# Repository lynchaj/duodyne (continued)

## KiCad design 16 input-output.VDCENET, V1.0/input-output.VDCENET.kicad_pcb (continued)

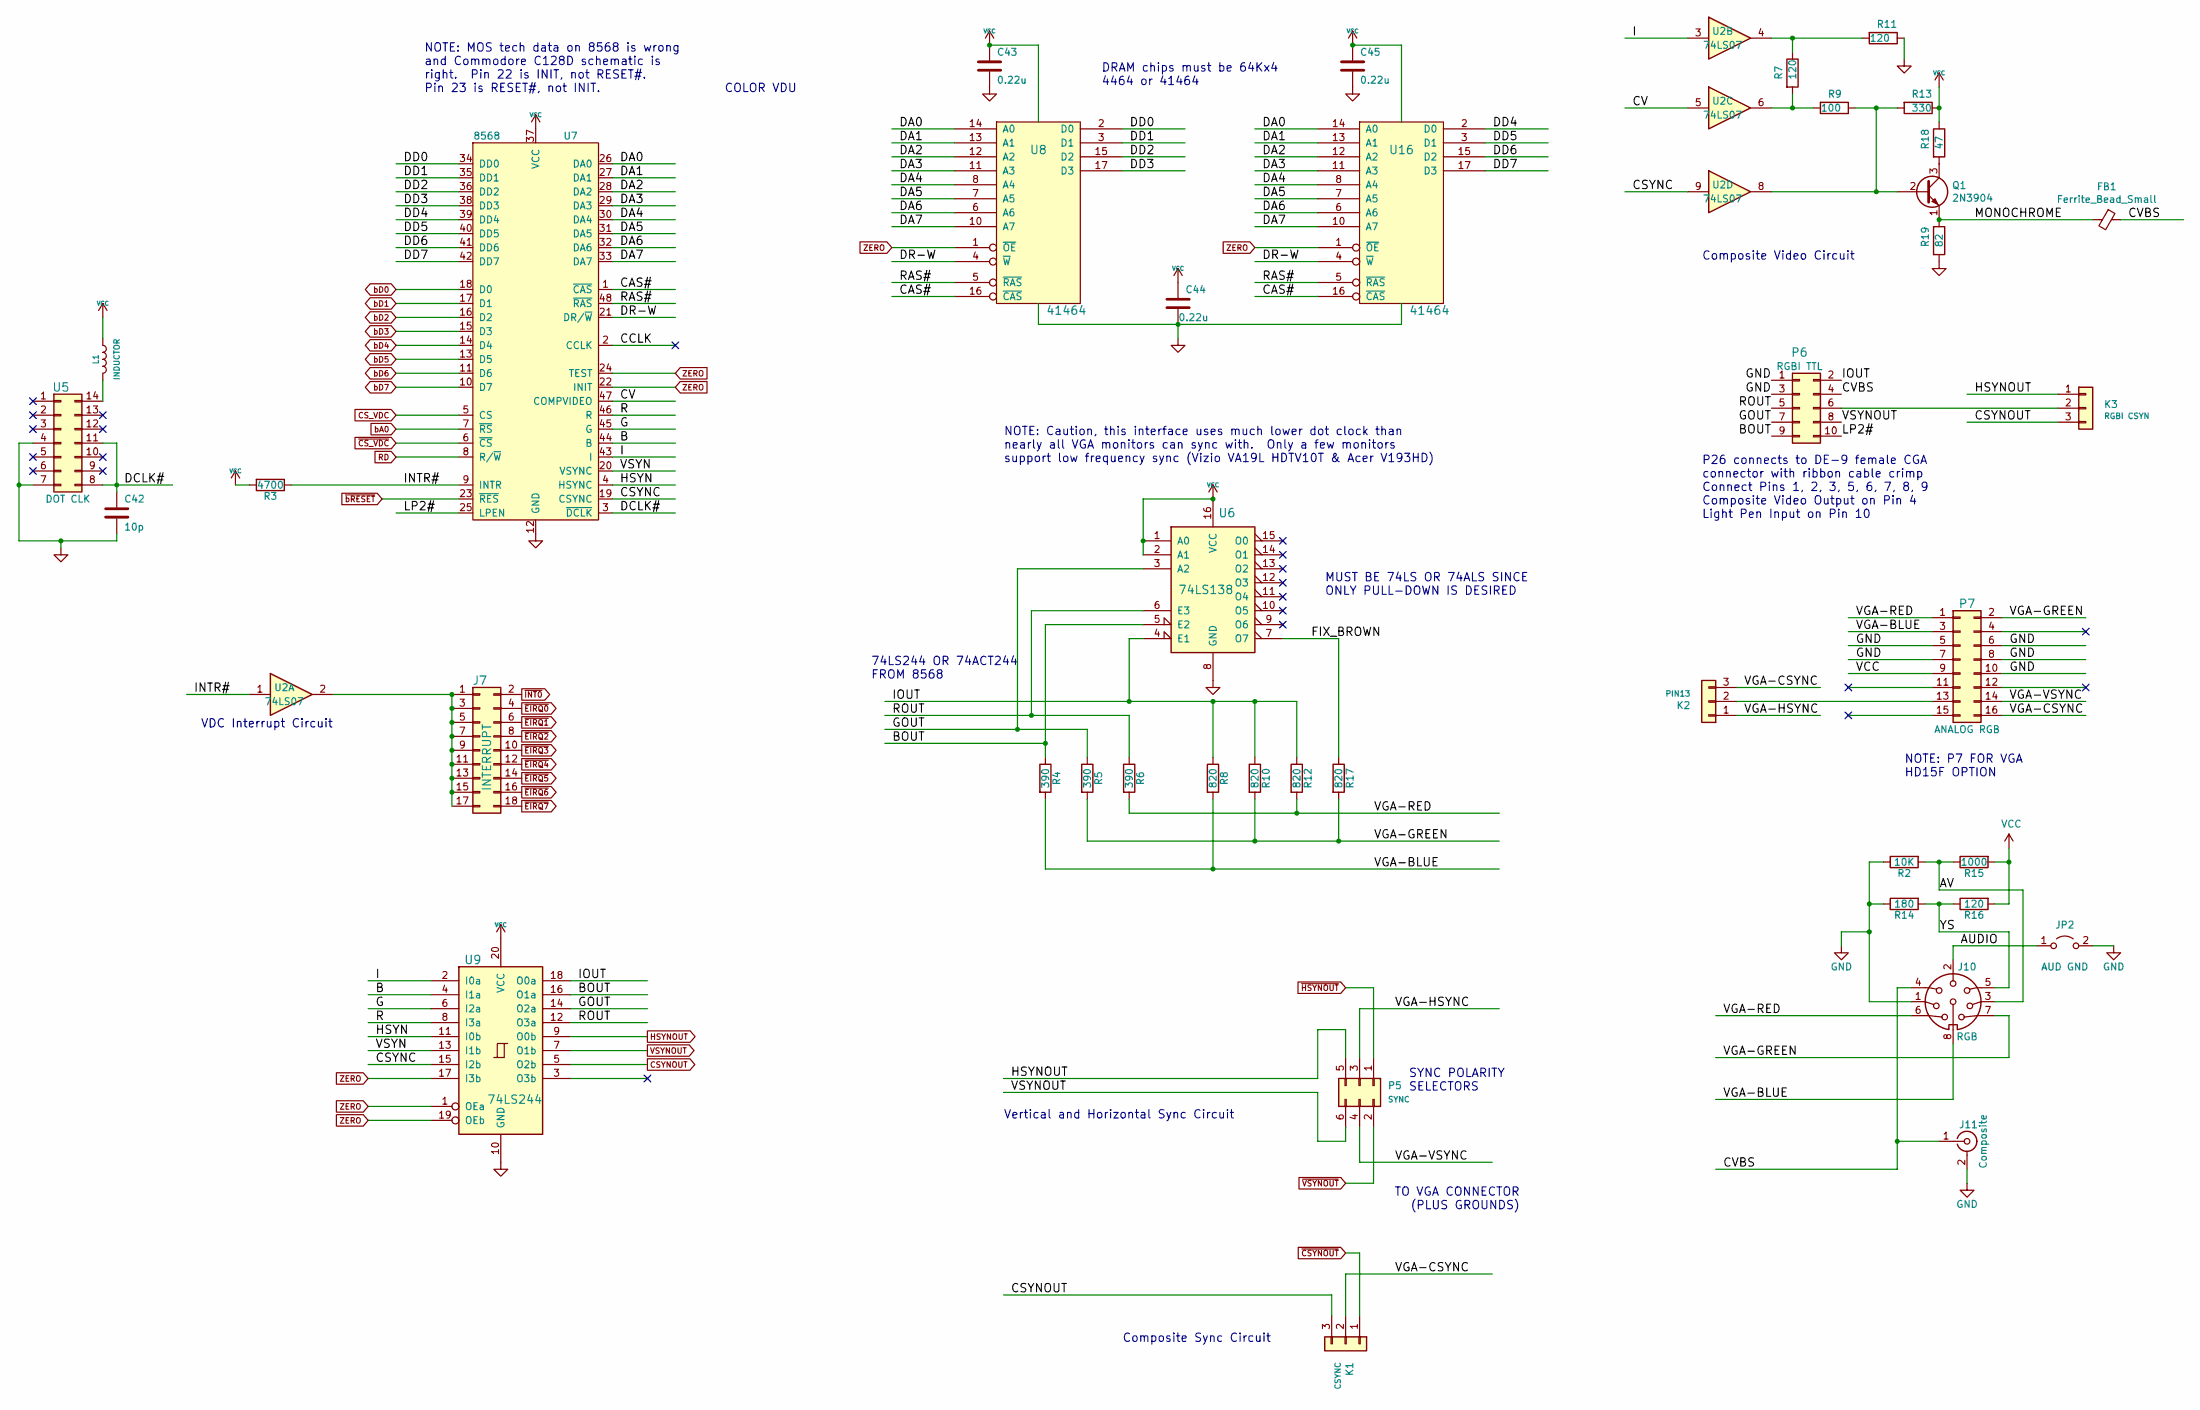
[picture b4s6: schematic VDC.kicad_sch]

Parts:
C42: 10p; C_Disc_D5.0mm_W2.5mm_P5.00mm
C43, C44, C45: 0.22u; C_Disc_D5.0mm_W2.5mm_P5.00mm
FB1: Ferrite_Bead_Small; LairdTech_28C0236-0JW-10
J7: INTERRUPT; PinHeader_2x09_P2.54mm_Vertical
J10: RGB; Conn_DIN_8pin
J11: Composite; Conn_RCA_Right
JP2: AUD GND; PinHeader_1x02_P2.54mm_Vertical
K1: CSYNC; PinHeader_1x03_P2.54mm_Vertical
K2: PIN13; PinHeader_1x03_P2.54mm_Vertical
K3: RGBI CSYN; PinHeader_1x03_P2.54mm_Vertical
L1: INDUCTOR; L_Axial_L6.6mm_D2.7mm_P10.16mm_Horizontal_Vishay_IM-2
P5: SYNC; PinHeader_2x03_P2.54mm_Vertical
P6: RGBI TTL; IDC-Header_2x05_P2.54mm_Horizontal
P7: ANALOG RGB; IDC-Header_2x08_P2.54mm_Horizontal
Q1: 2N3904; TO-92L_Inline
R2: 10K; R_Axial_DIN0207_L6.3mm_D2.5mm_P7.62mm_Horizontal
R3: 4700; R_Axial_DIN0207_L6.3mm_D2.5mm_P7.62mm_Horizontal
R4, R5, R6: 390; R_Axial_DIN0207_L6.3mm_D2.5mm_P7.62mm_Horizontal
R7, R11, R16: 120; R_Axial_DIN0207_L6.3mm_D2.5mm_P7.62mm_Horizontal
R8, R10, R12, R17: 820; R_Axial_DIN0207_L6.3mm_D2.5mm_P7.62mm_Horizontal
R9: 100; R_Axial_DIN0207_L6.3mm_D2.5mm_P7.62mm_Horizontal
R13: 330; R_Axial_DIN0207_L6.3mm_D2.5mm_P7.62mm_Horizontal
R14: 180; R_Axial_DIN0207_L6.3mm_D2.5mm_P7.62mm_Horizontal
R15: 1000; R_Axial_DIN0207_L6.3mm_D2.5mm_P7.62mm_Horizontal
R18: 47; R_Axial_DIN0207_L6.3mm_D2.5mm_P7.62mm_Horizontal
R19: 82; R_Axial_DIN0207_L6.3mm_D2.5mm_P7.62mm_Horizontal
U2: 74LS07; DIP-14_W7.62mm
U5: DOT CLK; DIP-14_W7.62mm
U6: 74LS138; DIP-16_W7.62mm
U7: 8568; DIP-48_W15.24mm
U8, U16: 41464; DIP-18_W7.62mm
U9: 74LS244; DIP-20_W7.62mm

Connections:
/VDC/AUDIO: J10.2, JP2.1 (A)
/VDC/AV: J10.3, R2.2, R15.1
/VDC/B: U7.44 (B), U9.4 (I1a)
/VDC/BOUT: P6.9, R4.1, U6.5 (E2), U9.16 (O1a)
/VDC/CAS#: U7.1 (~CAS), U8.16 (~CAS), U16.16 (~CAS)
/VDC/CCLK: U7.2 (CCLK)
/VDC/CSYNC: U2.9, U7.19 (CSYNC), U9.15 (I2b)
/VDC/CV: U2.5, U7.47 (COMPVIDEO)
/VDC/CVBS: FB1.1, J10.4, J11.1 (In), P6.4
/VDC/DA0: U7.26 (DA0), U8.14 (A0), U16.14 (A0)
/VDC/DA1: U7.27 (DA1), U8.13 (A1), U16.13 (A1)
/VDC/DA2: U7.28 (DA2), U8.12 (A2), U16.12 (A2)
/VDC/DA3: U7.29 (DA3), U8.11 (A3), U16.11 (A3)
/VDC/DA4: U7.30 (DA4), U8.8 (A4), U16.8 (A4)
/VDC/DA5: U7.31 (DA5), U8.7 (A5), U16.7 (A5)
/VDC/DA6: U7.32 (DA6), U8.6 (A6), U16.6 (A6)
/VDC/DA7: U7.33 (DA7), U8.10 (A7), U16.10 (A7)
/VDC/DCLK#: C42.1, U5.8, U5.11, U7.3 (~DCLK)
/VDC/DD0: U7.34 (DD0), U8.2 (D0)
/VDC/DD1: U7.35 (DD1), U8.3 (D1)
/VDC/DD2: U7.36 (DD2), U8.15 (D2)
/VDC/DD3: U7.38 (DD3), U8.17 (D3)
/VDC/DD4: U7.39 (DD4), U16.2 (D0)
/VDC/DD5: U7.40 (DD5), U16.3 (D1)
/VDC/DD6: U7.41 (DD6), U16.15 (D2)
/VDC/DD7: U7.42 (DD7), U16.17 (D3)
/VDC/DR-W: U7.21 (DR/~W), U8.4 (~W), U16.4 (~W)
/VDC/FIX_BROWN: R17.1, U6.7 (O7)
/VDC/G: U7.45 (G), U9.6 (I2a)
/VDC/GOUT: P6.7, R5.1, U6.3 (A2), U9.14 (O2a)
/VDC/HSYN: U7.4 (HSYNC), U9.11 (I0b)
/VDC/I: U2.3, U7.43 (I), U9.2 (I0a)
/VDC/INTR#: R3.1, U2.1, U7.9 (INTR)
/VDC/IOUT: P6.2, R8.1, R10.1, R12.1, U6.4 (E1), U9.18 (O0a)
/VDC/LP2#: P6.10, U7.25 (LPEN)
/VDC/MONOCHROME: FB1.2, Q1.1 (E), R19.1
/VDC/R: U7.46 (R), U9.8 (I3a)
/VDC/RAS#: U7.48 (~RAS), U8.5 (~RAS), U16.5 (~RAS)
/VDC/ROUT: P6.5, R6.1, U6.6 (E3), U9.12 (O3a)
/VDC/VGA-BLUE: J10.8, P7.3, R4.2, R8.2
/VDC/VGA-CSYNC: K1.2, K2.3, P7.16
/VDC/VGA-GREEN: J10.7, P7.2, R5.2, R10.2, R17.2
/VDC/VGA-HSYNC: K2.1, P5.3
/VDC/VGA-RED: J10.6, P7.1, R6.2, R12.2
/VDC/VGA-VSYNC: P5.4, P7.14
/VDC/VSYN: U7.20 (VSYNC), U9.13 (I1b)
/VDC/YS: J10.5, R14.2, R16.1
CSYNOUT: K1.3, K3.3, U9.5 (O2b); also elsewhere on the board
CS_VDC: U7.5 (CS); also elsewhere on the board
GND: C42.2, C43.2, C44.2, C45.2, J10.1, J11.2 (Ext), JP2.2 (B), P6.1, P6.3, P7.5, P7.6, P7.7, P7.8, P7.10, R2.1, R11.1, R14.1, R19.2, U5.4, U5.7, U6.8 (GND), U7.12 (GND), U8.18 (GND), U9.10 (GND), U16.18 (GND); also elsewhere on the board
HSYNOUT: K3.1, P5.5, U9.9 (O0b); also elsewhere on the board
unnamed: J7.1, J7.3, J7.5, J7.7, J7.9, J7.11, J7.13, J7.15, J7.17, U2.2
unnamed: K2.2, P7.13
unnamed: K3.2, P6.6
unnamed: L1.2, U5.14
unnamed: Q1.2 (B), R9.1, R13.2, U2.8
unnamed: Q1.3 (C), R18.2
unnamed: R7.2, R9.2, U2.6
unnamed: R7.1, R11.2, U2.4
RD: U7.8 (R/~W); also elsewhere on the board
VCC: C43.1, C44.1, C45.1, L1.1, P7.9, R3.2, R13.1, R15.2, R16.2, R18.1, U6.1 (A0), U6.2 (A1), U6.16 (VCC), U7.37 (VCC), U8.9 (VCC), U9.20 (VCC), U16.9 (VCC); also elsewhere on the board
VSYNOUT: P5.6, P6.8, U9.7 (O1b); also elsewhere on the board
ZERO: U7.22 (INIT), U7.24 (TEST), U8.1 (~OE), U9.1 (OEa), U9.17 (I3b), U9.19 (OEb), U16.1 (~OE); also elsewhere on the board
bA0: U7.7 (~RS); also elsewhere on the board
bD0: U7.18 (D0); also elsewhere on the board
bD1: U7.17 (D1); also elsewhere on the board
bD2: U7.16 (D2); also elsewhere on the board
bD3: U7.15 (D3); also elsewhere on the board
bD4: U7.14 (D4); also elsewhere on the board
bD5: U7.13 (D5); also elsewhere on the board
bD6: U7.11 (D6); also elsewhere on the board
bD7: U7.10 (D7); also elsewhere on the board
~CSYNOUT: K1.1; also elsewhere on the board
~CS_VDC: U7.6 (~CS); also elsewhere on the board
~HSYNOUT: P5.1; also elsewhere on the board
~VSYNOUT: P5.2; also elsewhere on the board
~bRESET: U7.23 (~RES); also elsewhere on the board

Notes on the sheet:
VDC Interrupt Circuit
Composite Sync Circuit
Vertical and Horizontal Sync Circuit
74LS244 OR 74ACT244 FROM 8568
NOTE: Caution, this interface uses much lower dot clock than nearly all VGA monitors can sync with. Only a few monitors support low frequency sync (Vizio VA19L HDTV10T & Acer V193HD)
SYNC POLARITY SELECTORS
Composite Video Circuit
COLOR VDU
DRAM chips must be 64Kx4 4464 or 41464
TO VGA CONNECTOR (PLUS GROUNDS)
P26 connects to DE-9 female CGA connector with ribbon cable crimp Connect Pins 1, 2, 3, 5, 6, 7, 8, 9 Composite Video Output on Pin 4 Light Pen Input on Pin 10
NOTE: P7 FOR VGA HD15F OPTION
MUST BE 74LS OR 74ALS SINCE ONLY PULL-DOWN IS DESIRED
NOTE: MOS tech data on 8568 is wrong and Commodore C128D schematic is right. Pin 22 is INIT, not RESET#. Pin 23 is RESET#, not INIT.

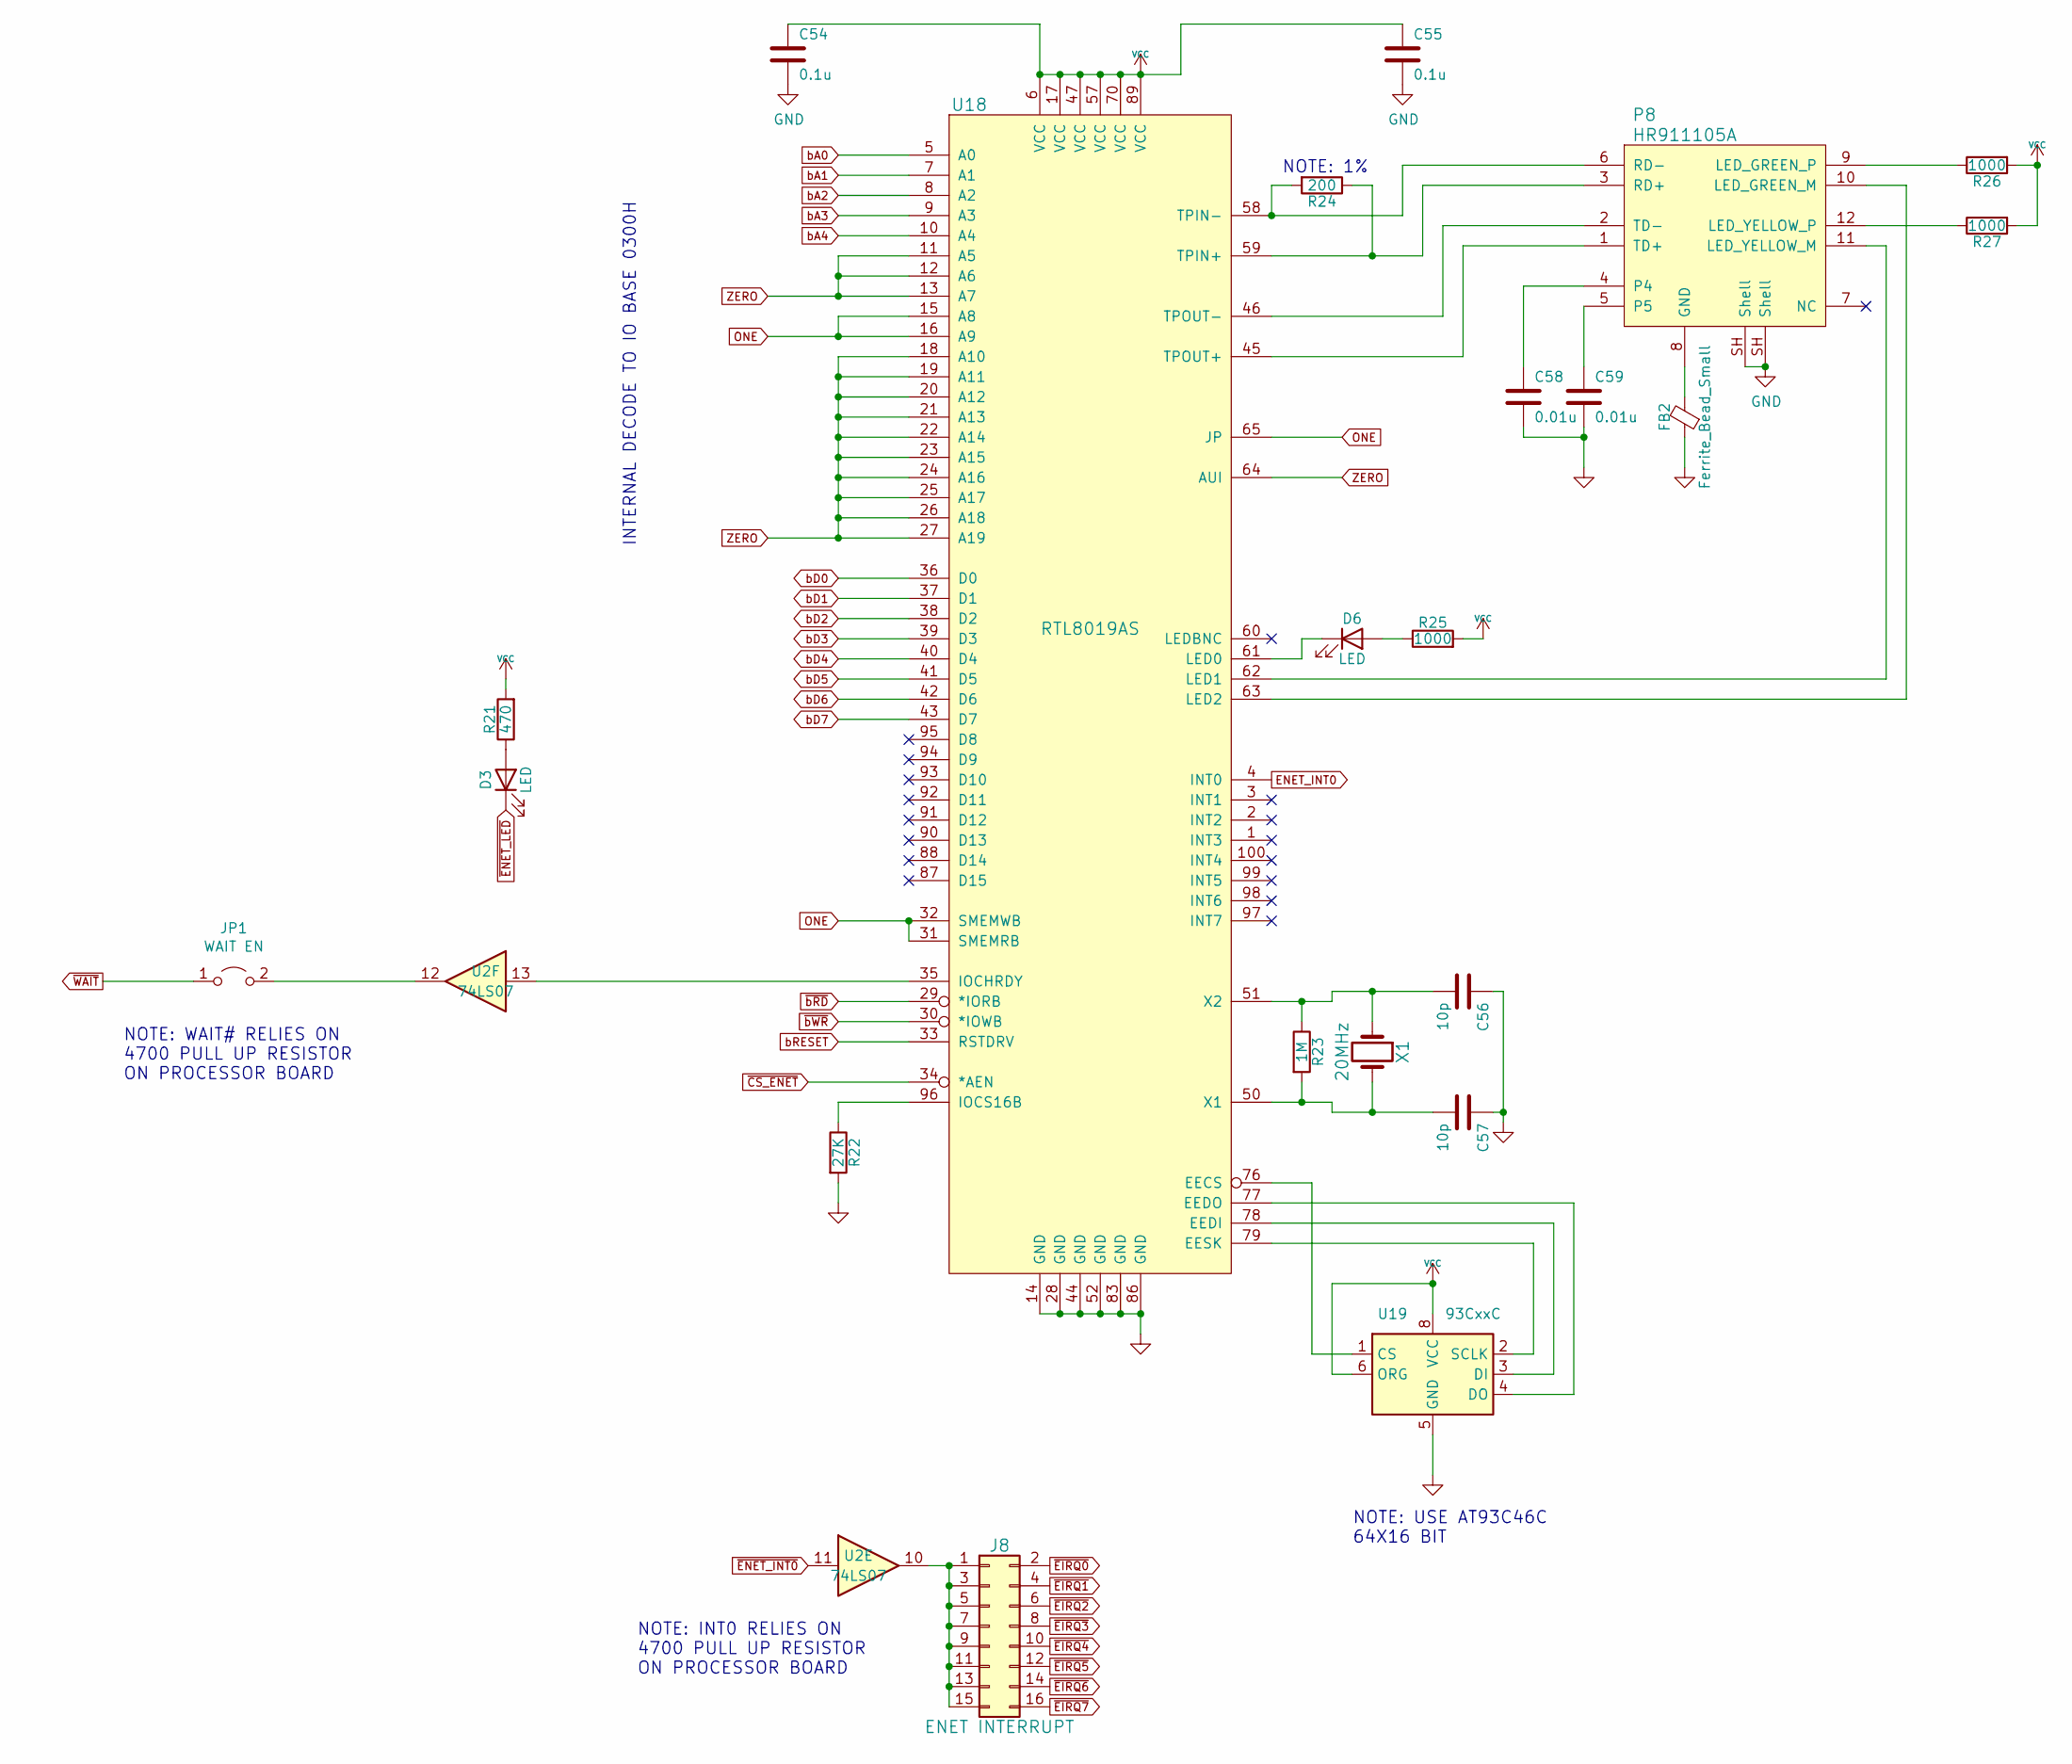
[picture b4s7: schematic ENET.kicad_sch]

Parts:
C54, C55: 0.1u; C_Disc_D5.0mm_W2.5mm_P5.00mm
C56, C57: 10p; C_Disc_D5.0mm_W2.5mm_P5.00mm
C58, C59: 0.01u; C_Disc_D5.0mm_W2.5mm_P5.00mm
D3, D6: LED; LED_D3.0mm_Horizontal_O3.81mm_Z2.0mm
FB2: Ferrite_Bead_Small; LairdTech_28C0236-0JW-10
J8: ENET INTERRUPT; PinHeader_2x08_P2.54mm_Vertical
JP1: WAIT EN; PinHeader_1x02_P2.54mm_Vertical
P8: HR911105A; RJ45_Hanrun_HR911105A
R21: 470; R_Axial_DIN0207_L6.3mm_D2.5mm_P7.62mm_Horizontal
R22: 27K; R_Axial_DIN0207_L6.3mm_D2.5mm_P7.62mm_Horizontal
R23: 1M; R_Axial_DIN0207_L6.3mm_D2.5mm_P7.62mm_Horizontal
R24: 200; R_Axial_DIN0207_L6.3mm_D2.5mm_P7.62mm_Horizontal
R25, R26, R27: 1000; R_Axial_DIN0207_L6.3mm_D2.5mm_P7.62mm_Horizontal
U2: 74LS07; DIP-14_W7.62mm_Socket
U18: RTL8019AS; QFP100-DIP-Adapter
U19: 93CxxC; DIP-8_W7.62mm_Socket
X1: 20MHz; Crystal_HC49-4H_Vertical

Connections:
ENET_INT0: U18.4 (INT0); also elsewhere on the board
GND: C54.2, C55.2, C56.1, C57.1, C58.2, C59.2, FB2.1, P8.SH (Shell), R22.2, U18.14 (GND), U18.28 (GND), U18.44 (GND), U18.52 (GND), U18.83 (GND), U18.86 (GND), U19.5 (GND); also elsewhere on the board
unnamed: C56.2, R23.1, U18.51 (X2), X1.1
unnamed: C57.2, R23.2, U18.50 (X1), X1.2
unnamed: C58.1, P8.4
unnamed: C59.1, P8.5
unnamed: D3.2 (A), R21.1
unnamed: D6.1 (K), U18.61 (LED0)
unnamed: D6.2 (A), R25.1
unnamed: FB2.2, P8.8 (GND)
unnamed: J8.1, J8.3, J8.5, J8.7, J8.9, J8.11, J8.13, J8.15, U2.10
unnamed: JP1.2 (B), U2.12
unnamed: P8.1 (TD+), U18.45 (TPOUT+)
unnamed: P8.2 (TD-), U18.46 (TPOUT-)
unnamed: P8.3 (RD+), R24.1, U18.59 (TPIN+)
unnamed: P8.6 (RD-), R24.2, U18.58 (TPIN-)
unnamed: P8.9 (LED_GREEN_P), R26.1
unnamed: P8.10 (LED_GREEN_M), U18.63 (LED2)
unnamed: P8.11 (LED_YELLOW_M), U18.62 (LED1)
unnamed: P8.12 (LED_YELLOW_P), R27.1
unnamed: R22.1, U18.96 (IOCS16B)
unnamed: U2.13, U18.35 (IOCHRDY)
unnamed: U18.76 (EECS), U19.1 (CS)
unnamed: U18.77 (EEDO), U19.4 (DO)
unnamed: U18.78 (EEDI), U19.3 (DI)
unnamed: U18.79 (EESK), U19.2 (SCLK)
ONE: U18.15 (A8), U18.16 (A9), U18.31 (SMEMRB), U18.32 (SMEMWB), U18.65 (JP); also elsewhere on the board
VCC: C54.1, C55.1, R21.2, R25.2, R26.2, R27.2, U18.6 (VCC), U18.17 (VCC), U18.47 (VCC), U18.57 (VCC), U18.70 (VCC), U18.89 (VCC), U19.6 (ORG), U19.8 (VCC); also elsewhere on the board
ZERO: U18.11 (A5), U18.12 (A6), U18.13 (A7), U18.18 (A10), U18.19 (A11), U18.20 (A12), U18.21 (A13), U18.22 (A14), U18.23 (A15), U18.24 (A16), U18.25 (A17), U18.26 (A18), U18.27 (A19), U18.64 (AUI); also elsewhere on the board
bA0: U18.5 (A0); also elsewhere on the board
bA1: U18.7 (A1); also elsewhere on the board
bA2: U18.8 (A2); also elsewhere on the board
bA3: U18.9 (A3); also elsewhere on the board
bA4: U18.10 (A4); also elsewhere on the board
bD0: U18.36 (D0); also elsewhere on the board
bD1: U18.37 (D1); also elsewhere on the board
bD2: U18.38 (D2); also elsewhere on the board
bD3: U18.39 (D3); also elsewhere on the board
bD4: U18.40 (D4); also elsewhere on the board
bD5: U18.41 (D5); also elsewhere on the board
bD6: U18.42 (D6); also elsewhere on the board
bD7: U18.43 (D7); also elsewhere on the board
bRESET: U18.33 (RSTDRV); also elsewhere on the board
~CS_ENET: U18.34 (*AEN); also elsewhere on the board
~ENET_INT0: U2.11; also elsewhere on the board
~ENET_LED: D3.1 (K); also elsewhere on the board
~WAIT: JP1.1 (A); also elsewhere on the board
~bRD: U18.29 (*IORB); also elsewhere on the board
~bWR: U18.30 (*IOWB); also elsewhere on the board

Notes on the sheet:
NOTE: INT0 RELIES ON 4700 PULL UP RESISTOR ON PROCESSOR BOARD
NOTE: USE AT93C46C 64X16 BIT
NOTE: 1%
NOTE: WAIT# RELIES ON 4700 PULL UP RESISTOR ON PROCESSOR BOARD
INTERNAL DECODE TO IO BASE 0300H

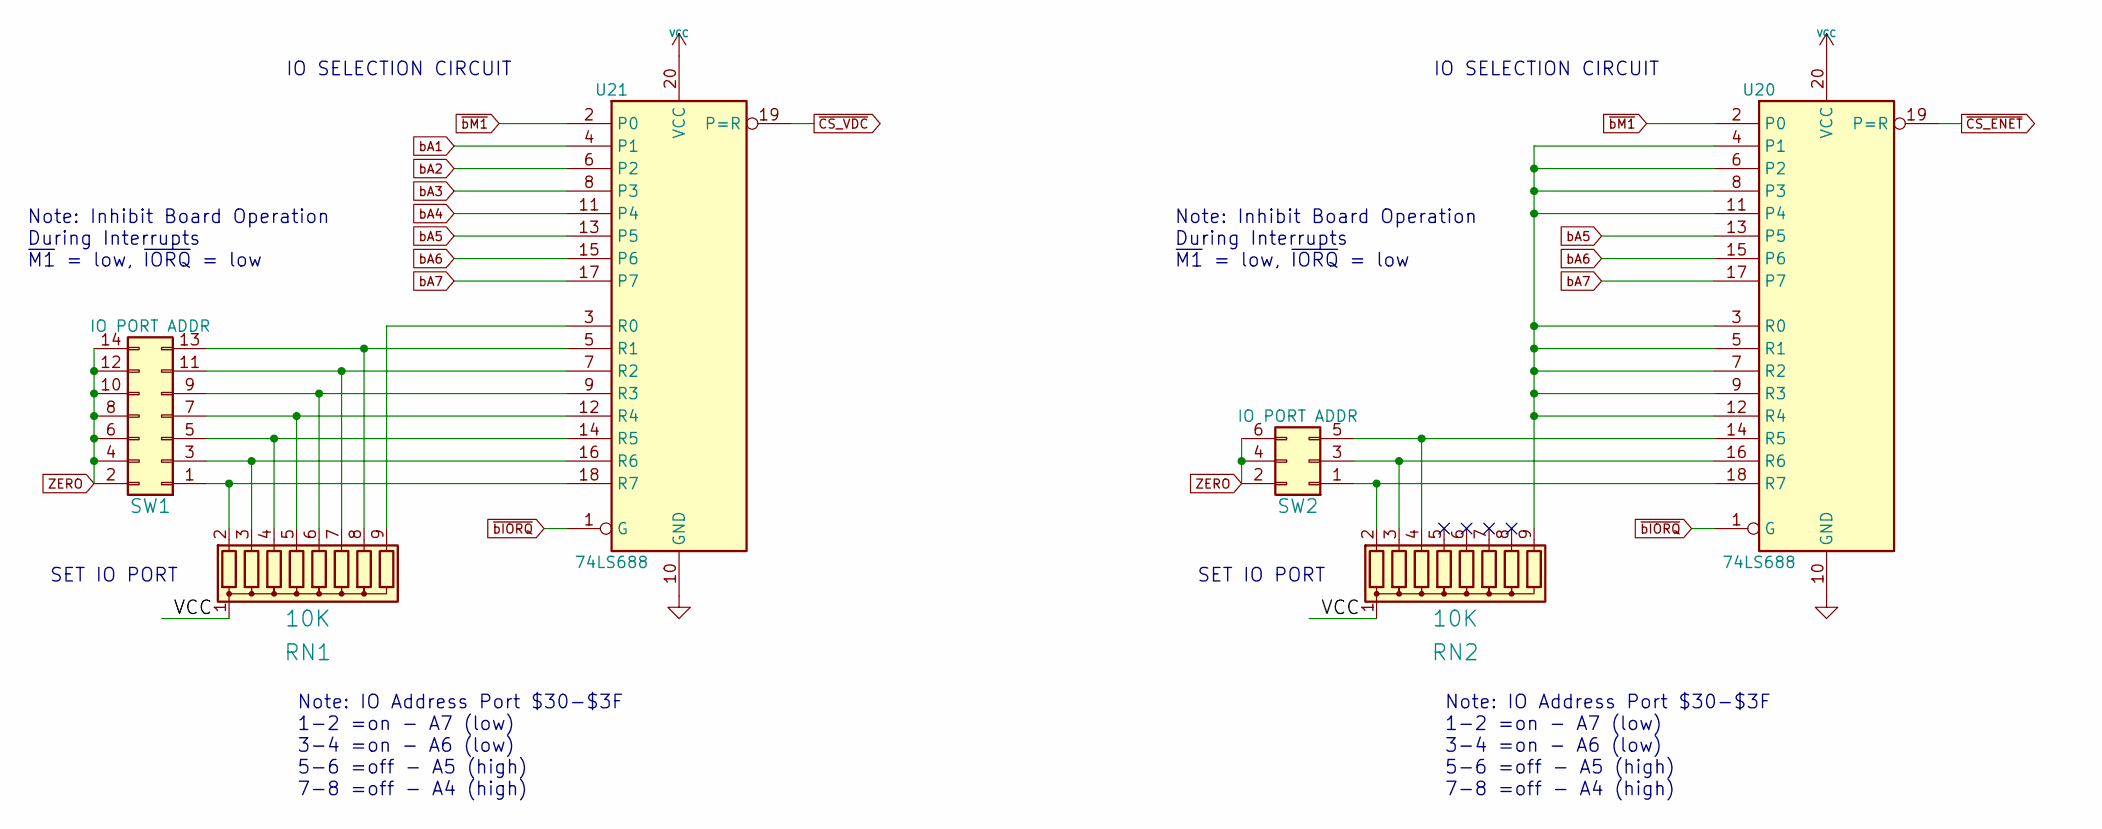
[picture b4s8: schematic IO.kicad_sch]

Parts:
RN1, RN2: 10K; R_Array_SIP9
SW1: IO PORT ADDR; PinHeader_2x07_P2.54mm_Vertical
SW2: IO PORT ADDR; PinHeader_2x03_P2.54mm_Vertical
U20, U21: 74LS688; DIP-20_W7.62mm_Socket

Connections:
GND: U20.10 (GND), U21.10 (GND); also elsewhere on the board
unnamed: RN1.2 (R1), SW1.1, U21.18 (R7)
unnamed: RN1.3 (R2), SW1.3, U21.16 (R6)
unnamed: RN1.4 (R3), SW1.5, U21.14 (R5)
unnamed: RN1.5 (R4), SW1.7, U21.12 (R4)
unnamed: RN1.6 (R5), SW1.9, U21.9 (R3)
unnamed: RN1.7 (R6), SW1.11, U21.7 (R2)
unnamed: RN1.8 (R7), SW1.13, U21.5 (R1)
unnamed: RN1.9 (R8), U21.3 (R0)
unnamed: RN2.2 (R1), SW2.1, U20.18 (R7)
unnamed: RN2.3 (R2), SW2.3, U20.16 (R6)
unnamed: RN2.4 (R3), SW2.5, U20.14 (R5)
unnamed: RN2.9 (R8), U20.3 (R0), U20.4 (P1), U20.5 (R1), U20.6 (P2), U20.7 (R2), U20.8 (P3), U20.9 (R3), U20.11 (P4), U20.12 (R4)
VCC: RN1.1 (common), RN2.1 (common), U20.20 (VCC), U21.20 (VCC); also elsewhere on the board
ZERO: SW1.2, SW1.4, SW1.6, SW1.8, SW1.10, SW1.12, SW1.14, SW2.2, SW2.4, SW2.6; also elsewhere on the board
bA1: U21.4 (P1); also elsewhere on the board
bA2: U21.6 (P2); also elsewhere on the board
bA3: U21.8 (P3); also elsewhere on the board
bA4: U21.11 (P4); also elsewhere on the board
bA5: U20.13 (P5), U21.13 (P5); also elsewhere on the board
bA6: U20.15 (P6), U21.15 (P6); also elsewhere on the board
bA7: U20.17 (P7), U21.17 (P7); also elsewhere on the board
~CS_ENET: U20.19 (P=R); also elsewhere on the board
~CS_VDC: U21.19 (P=R); also elsewhere on the board
~bIORQ: U20.1 (G), U21.1 (G); also elsewhere on the board
~bM1: U20.2 (P0), U21.2 (P0); also elsewhere on the board

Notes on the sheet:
SET IO PORT
Note: Inhibit Board Operation During Interrupts ~{M1} = low, ~{IORQ} = low
Note: IO Address Port $30-$3F 1-2 =on - A7 (low) 3-4 =on - A6 (low) 5-6 =off - A5 (high) 7-8 =off - A4 (high)
IO SELECTION CIRCUIT

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
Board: 2 copper layers, 120 parts (0 on the bottom side), 171 nets, no tracks yet.

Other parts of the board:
D2: LED; LED_D3.0mm_Horizontal_O3.81mm_Z2.0mm
R20: 470; R_Axial_DIN0207_L6.3mm_D2.5mm_P7.62mm_Horizontal

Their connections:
unnamed: D2.2 (A), R20.1
VCC: R20.2; also elsewhere on the board
~VDC_LED: D2.1 (K); also elsewhere on the board

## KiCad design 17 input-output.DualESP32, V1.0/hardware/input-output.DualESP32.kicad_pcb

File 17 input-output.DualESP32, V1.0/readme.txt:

The template prototyping board is intended to be the basis for future board development by capturing the specifications for the board outline, connectors, and the external bus.

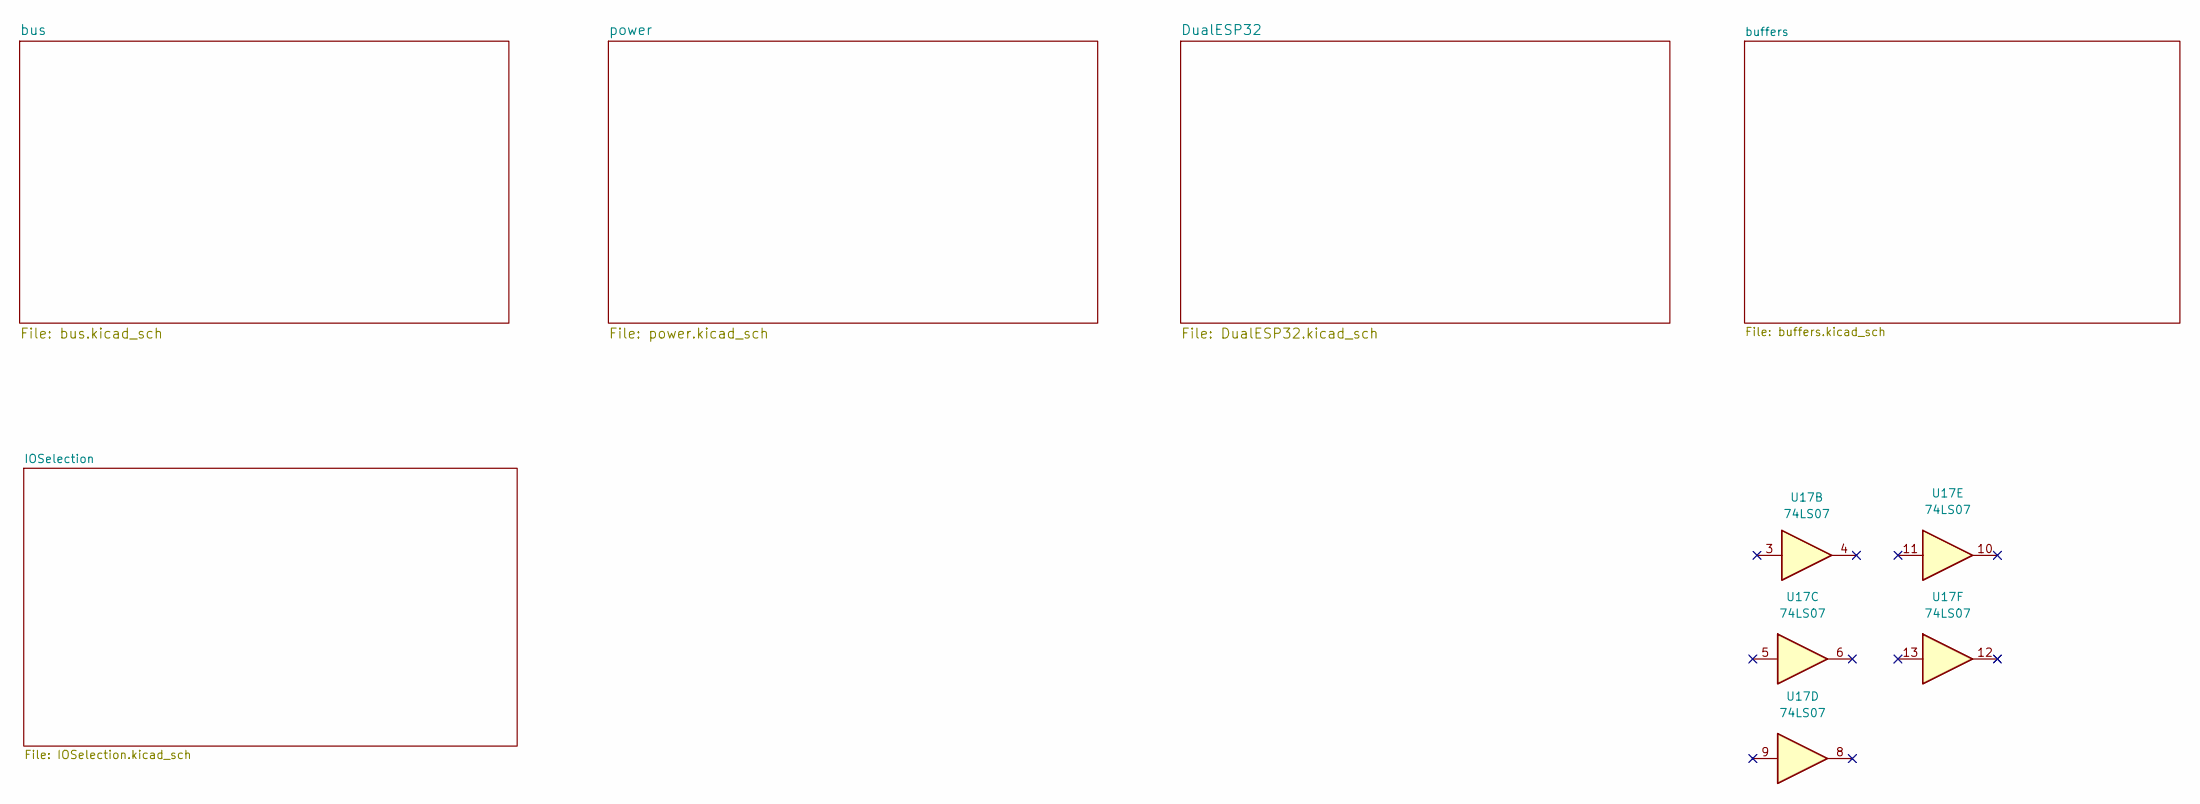
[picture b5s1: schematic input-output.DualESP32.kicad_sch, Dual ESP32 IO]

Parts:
U17: 74LS07; DIP-14_W7.62mm
